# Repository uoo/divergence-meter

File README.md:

# divergence-meter
Arduino code and PCB design for Stein's Gate divergence meter prop

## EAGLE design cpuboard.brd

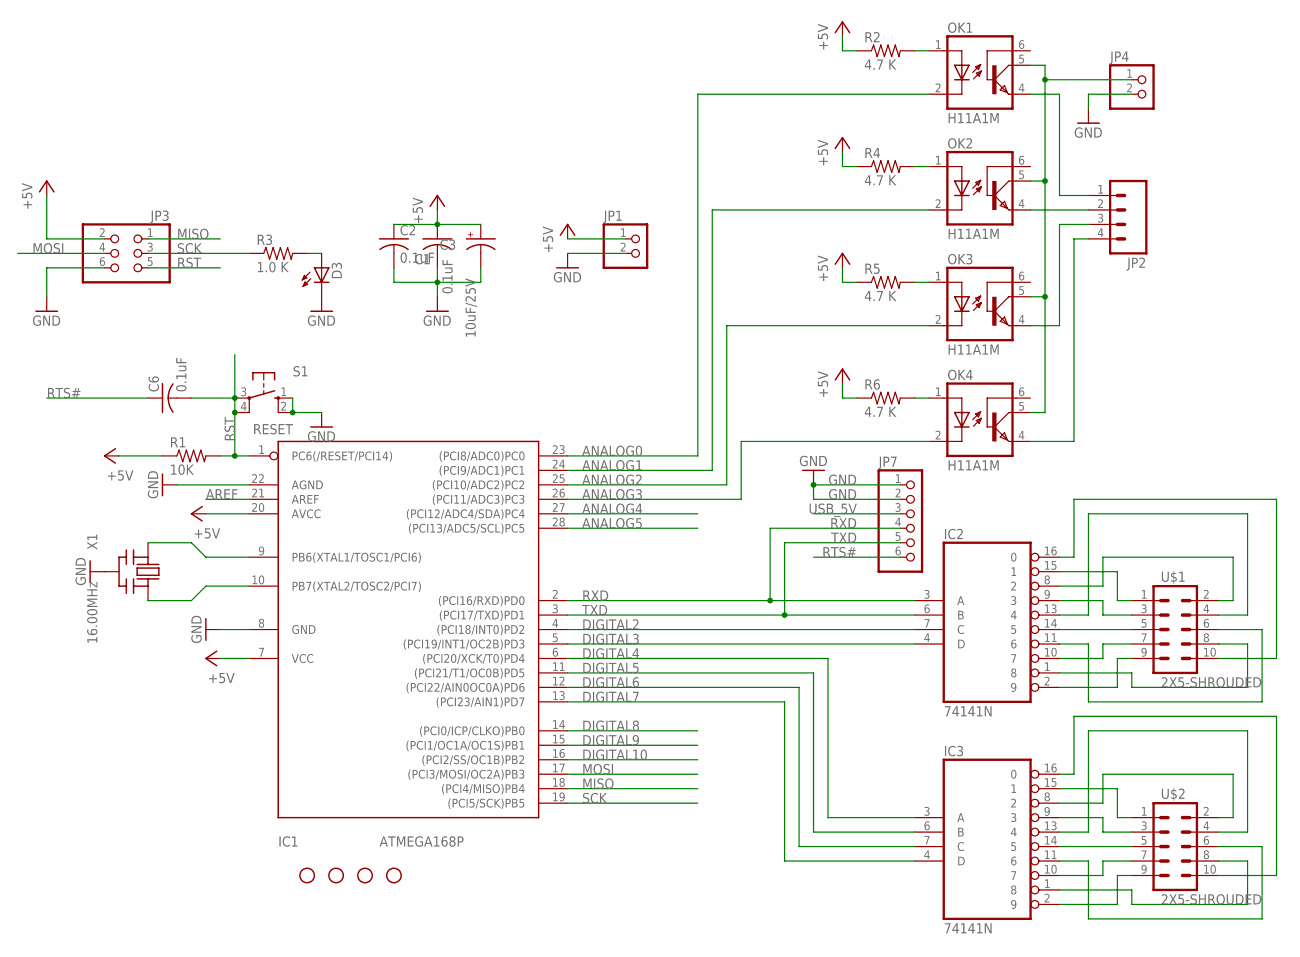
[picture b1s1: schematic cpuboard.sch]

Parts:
C1, C2, C6: 0.1uF; C025-025X050
C3: 10uF/25V; E2,5-6
D3: Green; LED3MM
IC1: ATMEGA168P; DIL28/3
IC2, IC3: 74141N; DIL16
JP1, JP4: PINHD-1X2CB; 1X02-CB
JP2: M04PTH; 1X04
JP3: PINHD-2X3; 2X03
JP7: PINHD-1X6CLEAN; 1X06-CLEAN
OK1, OK2, OK3, OK4: H11A1M; DIL06
R1: 10K; 0207/5V
R2, R4, R5, R6: 4.7 K; 0207/5V
R3: 1.0 K; 0207/5V
S1: RESET; B3F-10XX
STANDOFF1, STANDOFF2, STANDOFF3, STANDOFF4: STAND-OFF
U$1, U$2: 2X5-SHROUDED
X1: 16.00MHz; CERM_OSC

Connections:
+5V: C1.1, C2.1, C3.+, IC1.7 (VCC), IC1.20 (AVCC), JP1.1, JP3.2, R1.1, R2.1, R4.1, R5.1, R6.1
ANALOG0: IC1.23 ((PCI8/ADC0)PC0), OK1.2 (C)
ANALOG1: IC1.24 ((PCI9/ADC1)PC1), OK2.2 (C)
ANALOG2: IC1.25 ((PCI10/ADC2)PC2), OK3.2 (C)
ANALOG3: IC1.26 ((PCI11/ADC3)PC3), OK4.2 (C)
ANALOG4: IC1.27 ((PCI12/ADC4/SDA)PC4)
ANALOG5: IC1.28 ((PCI13/ADC5/SCL)PC5)
AREF: IC1.21 (AREF)
DIGITAL2: IC1.4 ((PCI18/INT0)PD2), IC2.7 (C)
DIGITAL3: IC1.5 ((PCI19/INT1/OC2B)PD3), IC2.4 (D)
DIGITAL4: IC1.6 ((PCI20/XCK/T0)PD4), IC3.3 (A)
DIGITAL5: IC1.11 ((PCI21/T1/OC0B)PD5), IC3.6 (B)
DIGITAL6: IC1.12 ((PCI22/AIN0OC0A)PD6), IC3.7 (C)
DIGITAL7: IC1.13 ((PCI23/AIN1)PD7), IC3.4 (D)
DIGITAL8: IC1.14 ((PCI0/ICP/CLKO)PB0)
DIGITAL9: IC1.15 ((PCI1/OC1A/OC1S)PB1)
DIGITAL10: IC1.16 ((PCI2/SS/OC1B)PB2)
GND: C1.2, C2.2, C3.-, D3.K (C), IC1.8 (GND), IC1.22 (AGND), IC2.12 (GND), IC3.12 (GND), JP1.2, JP3.6, JP4.2, JP7.1, JP7.2, S1.1 (S), S1.2 (S1), X1.P$2 (GND)
MISO: IC1.18 ((PCI4/MISO)PB4), JP3.1
MOSI: IC1.17 ((PCI3/MOSI/OC2A)PB3), JP3.4
unnamed: IC1.9 (PB6(XTAL1/TOSC1/PCI6)), X1.P$1 (IN)
unnamed: IC1.10 (PB7(XTAL2/TOSC2/PCI7)), X1.P$3 (OUT)
unnamed: IC2.13 (4), U$1.4
unnamed: D3.A, R3.2
unnamed: IC2.15 (1), U$1.1
unnamed: IC2.9 (3), U$1.3
unnamed: IC2.14 (5), U$1.5
unnamed: IC2.10 (7), U$1.7
unnamed: IC2.2 (9), U$1.9
unnamed: IC2.8 (2), U$1.2
unnamed: IC2.1 (8), U$1.8
unnamed: IC2.11 (6), U$1.6
unnamed: IC2.16 (0), U$1.10
unnamed: IC3.15 (1), U$2.1
unnamed: IC3.9 (3), U$2.3
unnamed: IC3.14 (5), U$2.5
unnamed: IC3.10 (7), U$2.7
unnamed: IC3.2 (9), U$2.9
unnamed: IC3.8 (2), U$2.2
unnamed: IC3.1 (8), U$2.8
unnamed: IC3.11 (6), U$2.6
unnamed: IC3.13 (4), U$2.4
unnamed: IC3.16 (0), U$2.10
unnamed: OK4.1 (A), R6.2
unnamed: OK3.1 (A), R5.2
unnamed: OK2.1 (A), R4.2
unnamed: OK1.1 (A), R2.2
unnamed: JP2.1, OK1.4 (EMI)
unnamed: JP2.2, OK2.4 (EMI)
unnamed: JP2.3, OK3.4 (EMI)
unnamed: JP2.4, OK4.4 (EMI)
unnamed: JP4.1, OK1.5 (COL), OK2.5 (COL), OK3.5 (COL), OK4.5 (COL)
RST: C6.2, IC1.1 (PC6(/RESET/PCI14)), JP3.5, R1.2, S1.3, S1.4 (P1)
RTS#: C6.1, JP7.6
RXD: IC1.2 ((PCI16/RXD)PD0), IC2.3 (A), JP7.4
SCK: IC1.19 ((PCI5/SCK)PB5), JP3.3, R3.1
TXD: IC1.3 ((PCI17/TXD)PD1), IC2.6 (B), JP7.5
USB_5V: JP7.3
VCC: IC2.5 (VCC), IC3.5 (VCC)

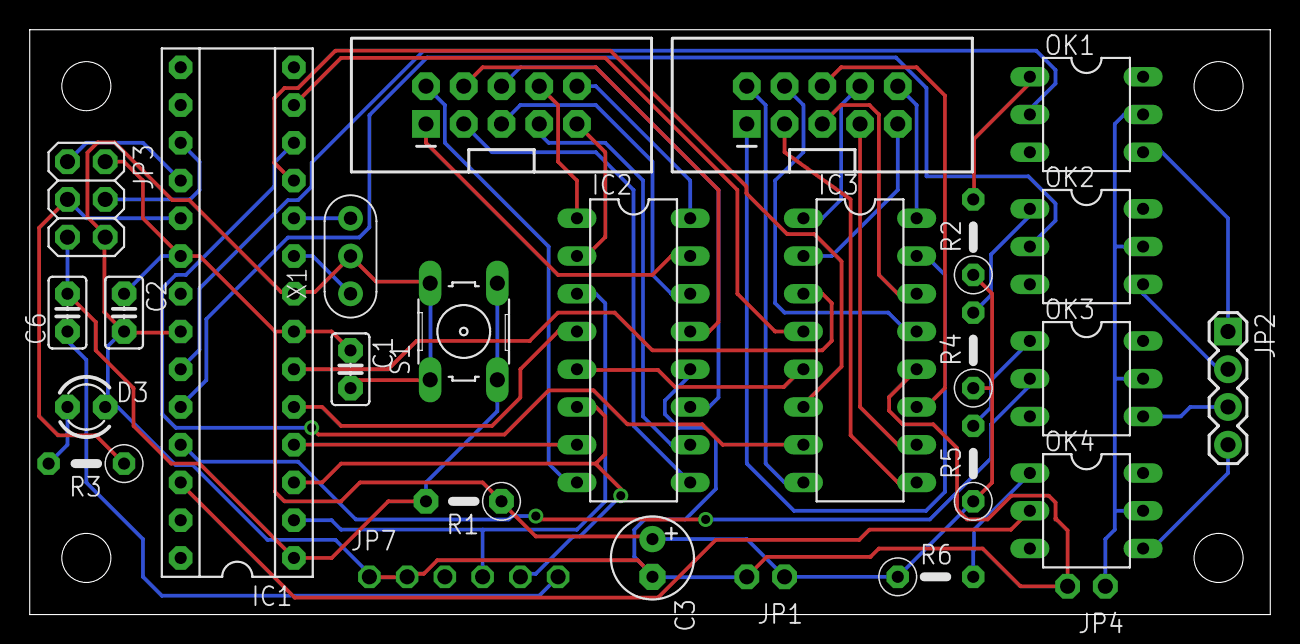
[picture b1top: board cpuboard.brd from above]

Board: 2 copper layers, 83.5 x 39.4 mm, 31 parts (0 on the bottom side), 52 nets.

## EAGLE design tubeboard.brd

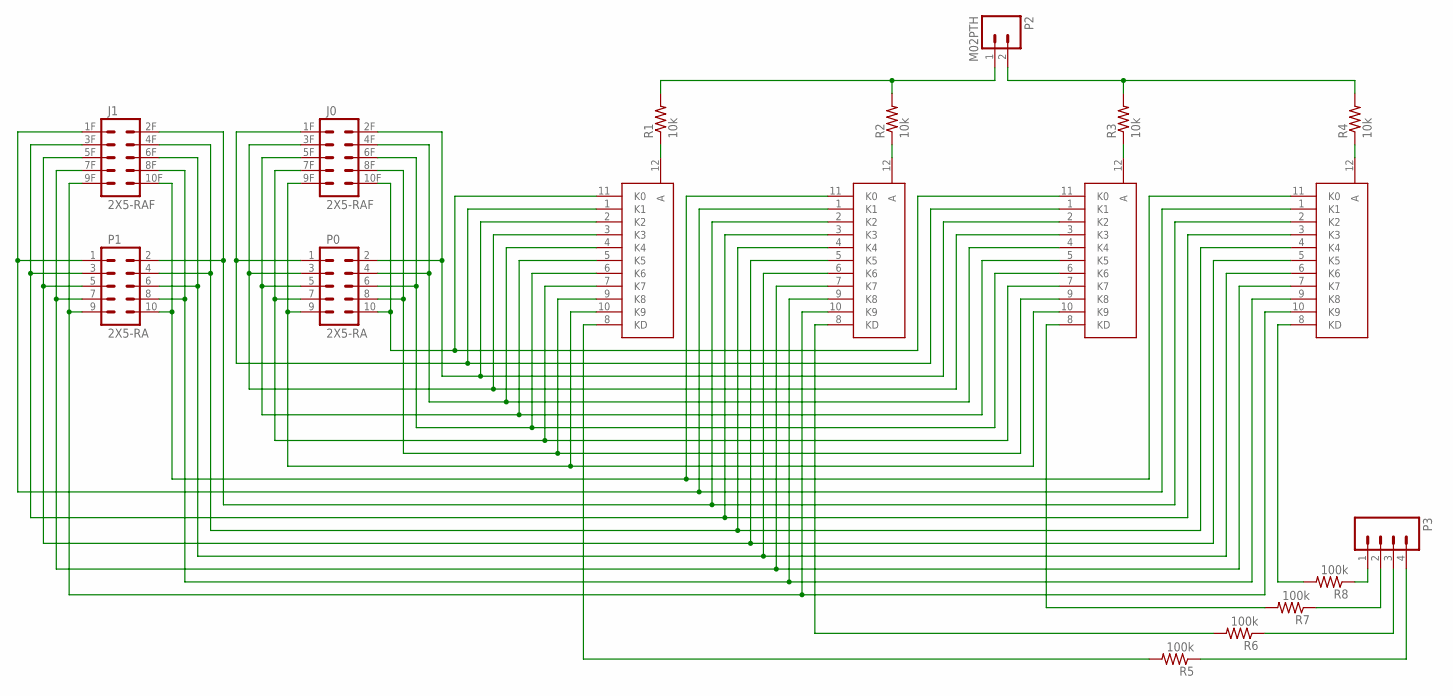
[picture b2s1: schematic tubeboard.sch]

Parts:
J0, J1: 2X5-RAF
P0, P1: 2X5-RA
P2: M02PTH; 1X02
P3: M04PTH; 1X04
R1, R2, R3, R4: 10k; AXIAL-0.5
R5, R6, R7, R8: 100k; AXIAL-0.5
V0, V1, V2, V3: IN-8-2-GRID

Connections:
unnamed: P2.1, R1.P$2 (2), R2.P$2 (2)
unnamed: P3.1, R8.P$1 (1)
unnamed: P3.2, R7.P$1 (1)
unnamed: P3.3, R6.P$1 (1)
unnamed: P3.4, R5.P$1 (1)
unnamed: J0.10F (10), P0.10, V0.11 (K0), V2.11 (K0)
unnamed: J0.9F (9), P0.9, V0.10 (K9), V2.10 (K9)
unnamed: J0.7F (7), P0.7, V0.7 (K7), V2.7 (K7)
unnamed: J0.5F (5), P0.5, V0.5 (K5), V2.5 (K5)
unnamed: J0.3F (3), P0.3, V0.3 (K3), V2.3 (K3)
unnamed: R1.P$1 (1), V0.12 (A)
unnamed: R2.P$1 (1), V1.12 (A)
unnamed: R3.P$1 (1), V2.12 (A)
unnamed: R4.P$1 (1), V3.12 (A)
unnamed: R5.P$2 (2), V0.8 (KD)
unnamed: R6.P$2 (2), V1.8 (KD)
unnamed: R7.P$2 (2), V2.8 (KD)
unnamed: R8.P$2 (2), V3.8 (KD)
unnamed: J0.1F (1), P0.1, V0.1 (K1), V2.1 (K1)
unnamed: J0.4F (4), P0.4, V0.4 (K4), V2.4 (K4)
unnamed: J1.10F (10), P1.10, V1.11 (K0), V3.11 (K0)
unnamed: J1.9F (9), P1.9, V1.10 (K9), V3.10 (K9)
unnamed: J1.1F (1), P1.1, V1.1 (K1), V3.1 (K1)
unnamed: J1.2F (2), P1.2, V1.2 (K2), V3.2 (K2)
unnamed: J1.3F (3), P1.3, V1.3 (K3), V3.3 (K3)
unnamed: J1.4F (4), P1.4, V1.4 (K4), V3.4 (K4)
unnamed: J1.5F (5), P1.5, V1.5 (K5), V3.5 (K5)
unnamed: J1.7F (7), P1.7, V1.7 (K7), V3.7 (K7)
unnamed: J0.6F (6), P0.6, V0.6 (K6), V2.6 (K6)
unnamed: J1.8F (8), P1.8, V1.9 (K8), V3.9 (K8)
unnamed: J1.6F (6), P1.6, V1.6 (K6), V3.6 (K6)
unnamed: P2.2, R3.P$2 (2), R4.P$2 (2)
unnamed: J0.2F (2), P0.2, V0.2 (K2), V2.2 (K2)
unnamed: J0.8F (8), P0.8, V0.9 (K8), V2.9 (K8)

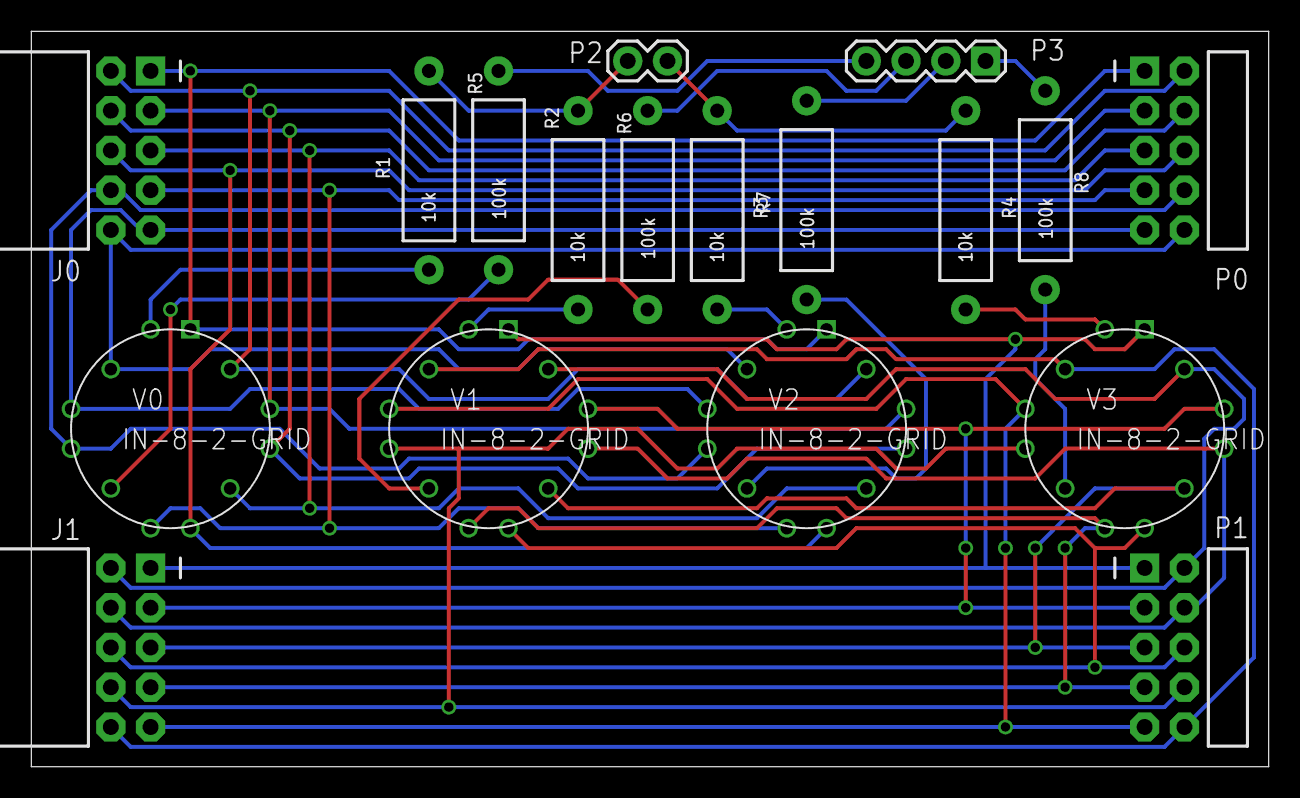
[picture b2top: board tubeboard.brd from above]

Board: 2 copper layers, 79.0 x 47.0 mm, 18 parts (0 on the bottom side), 34 nets.

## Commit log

2015-02-18 initial code
2015-02-18 rewrote digit scanner
2015-02-18 added switch and power supply enable
2015-02-18 code cleanup
2015-02-18 added Eagle files
2017-02-27 updated description to reflect presence of PCB designs

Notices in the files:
parts and their libraries:
SparkFun-Connectors: Licensing: Creative Commons ShareAlike 4.0 International - https://creativecommons.org/licenses/by-sa/4.0
